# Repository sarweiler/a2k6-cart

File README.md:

# A2k6 Cartridge

A cartridge PCB for the Atari 2600 for housing a 2732 EPROM and a 74LS04 hex inverter IC.

More photos:
* [Back side with 74LS04](images/pcb-back.jpg)
* [Inserted in an original Atari cartridge case](images/pcb-case.jpg)

## Producing a PCB

Download the [a2k6-cart-gerbers.zip](https://github.com/sarweiler/a2k6-cart/releases/latest/download/a2k6-cart-gerbers.zip) file for the latest release, upload the zip archive to a PCB manufacturer of your choice, and order a PCB. Make sure to choose 1.6 mm for PCB thickness (for many manufacturers this is the default) and choose a color for the solder mask that you like.

## EPROMs

So far I could only test it with one EPROM model, the National Semiconductors NMC27C32BQ200, because it's the only one I have on hand. Others with similar pin outs may work, too. If you've successfully tested one, feel free to message me, and I'll keep a list here.

## Using the PCB

The PCB fits in a standard Atari 2600 game cartridge case ([tested with a Starmaster case](images/pcb-case.jpg)). In my tests, the EPROM *with* a socket unfortunately was just a bit too thick, so if you plan to put the PCB in a case, I think the EPROM must be soldered to the PCB.

On the PCB, the side with the square pattern (the side with the EPROM) is the "label" side and must face towards the back of the console when inserting it.

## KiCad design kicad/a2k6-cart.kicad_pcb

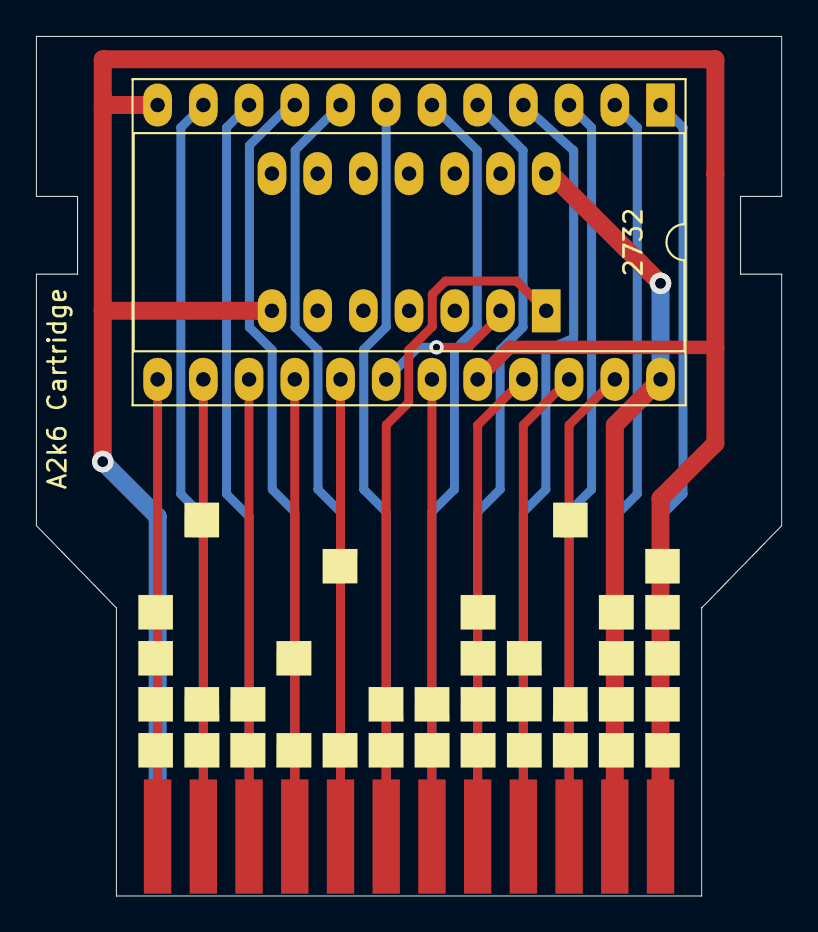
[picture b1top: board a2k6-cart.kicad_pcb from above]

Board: 2 copper layers, 41.4 x 47.8 mm, 3 parts (1 on the bottom side), 24 nets.

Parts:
J1: 2600_Cartridge_Port
U1: 2732; DIP-24_W15.24mm_Socket_LongPads
U2: 74LS04; DIP-14_W7.62mm_LongPads

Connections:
+5V: J1.+5V, U1.24, U2.14
D0: J1.D0, U1.9
D1: J1.D1, U1.10
D2: J1.D2, U1.11
D3: J1.D3, U1.13
D4: J1.D4, U1.14
D5: J1.D5, U1.15
D6: J1.D6, U1.16
D7: J1.D7, U1.17
GND: J1.GND, J1.SGND, U1.12, U1.20, U2.7
unnamed: J1.A0, U1.8
unnamed: J1.A1, U1.7
unnamed: J1.A2, U1.6
unnamed: J1.A3, U1.5
unnamed: J1.A4, U1.4
unnamed: J1.A5, U1.3
unnamed: J1.A6, U1.2
unnamed: J1.A7, U1.1
unnamed: J1.A8, U1.23
unnamed: J1.A9, U1.22
unnamed: J1.A10, U1.19
unnamed: J1.A11, U1.21
unnamed: J1.A12, U2.1
unnamed: U1.18, U2.2

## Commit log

2020-09-23 fix image file names
2020-09-23 link case image
2020-09-23 resize images
2020-09-23 take off 0.4 mm from the sides of the pcb
2020-09-23 remove file
2020-09-23 remove backup file
2020-09-23 add gerber files
